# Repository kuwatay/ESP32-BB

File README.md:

# ESP32-BB

## 1. Introduction

**ESP32-BB** (Bearbone) is yet another ESP-32 based development board. 
For the programming of the board, an *extended 7-pin FTDI adapter* is required.

## 2. Schematic

## 3. Board layout

## 4. BOM

|     Name   |          Parts                    |   Value                 |
|  :-------: | :-------------------------------: | :---------------------: |
|     U1     |  3.3V Low voltage drop Regulator  | LM1117-3.3              | 
|     U2     |  ESP-WROOM-32                     | -                       | 
|  LED1,LED2 |  LED1 (Green)  LED2(RED)          | (1608 size)             | 
|     J1     |  2.1mm power Jack                 | Power in                | 
|     J2     |  7 pin                            | L-angle connector       | 
|   J3,J4    |  10Pin x 2 receptacle             | pin header is ok        | 
|  SW1,SW2   |  Tactile Switch                   | Alps SKHH or equivalent | 
|   Q1,Q2    |  NPN-TR                           | (2SC2712)               | 
|   R1,R3    |  Carbon Register                  | 10K Ohm 1/10W(1608)     | 
|   R7,R8    |  Carbon Register                  | 1K Ohm 1/10W(1608)      | 
| R9,R10,R11 |  Carbon Register                  | 10K Ohm 1/10W(1608)     | 
|   R12,R13  |  Carbon Register                  | 1K Ohm 1/10W(1608)      | 
|     C2     |  Multilayer Ceramic Capacitor     | 1nF / 10V  (1608)       |
|     C6     |  Electrolytic  Capacitor          | 100uF / 10V or better   |
|     C7     |  Electrolytic  Capacitor          | 10uF / 10V or better    |
|     C8     |  Multilayer Ceramic  Capacitor    | 0.1uF / 10V (1608)      |

## EOF

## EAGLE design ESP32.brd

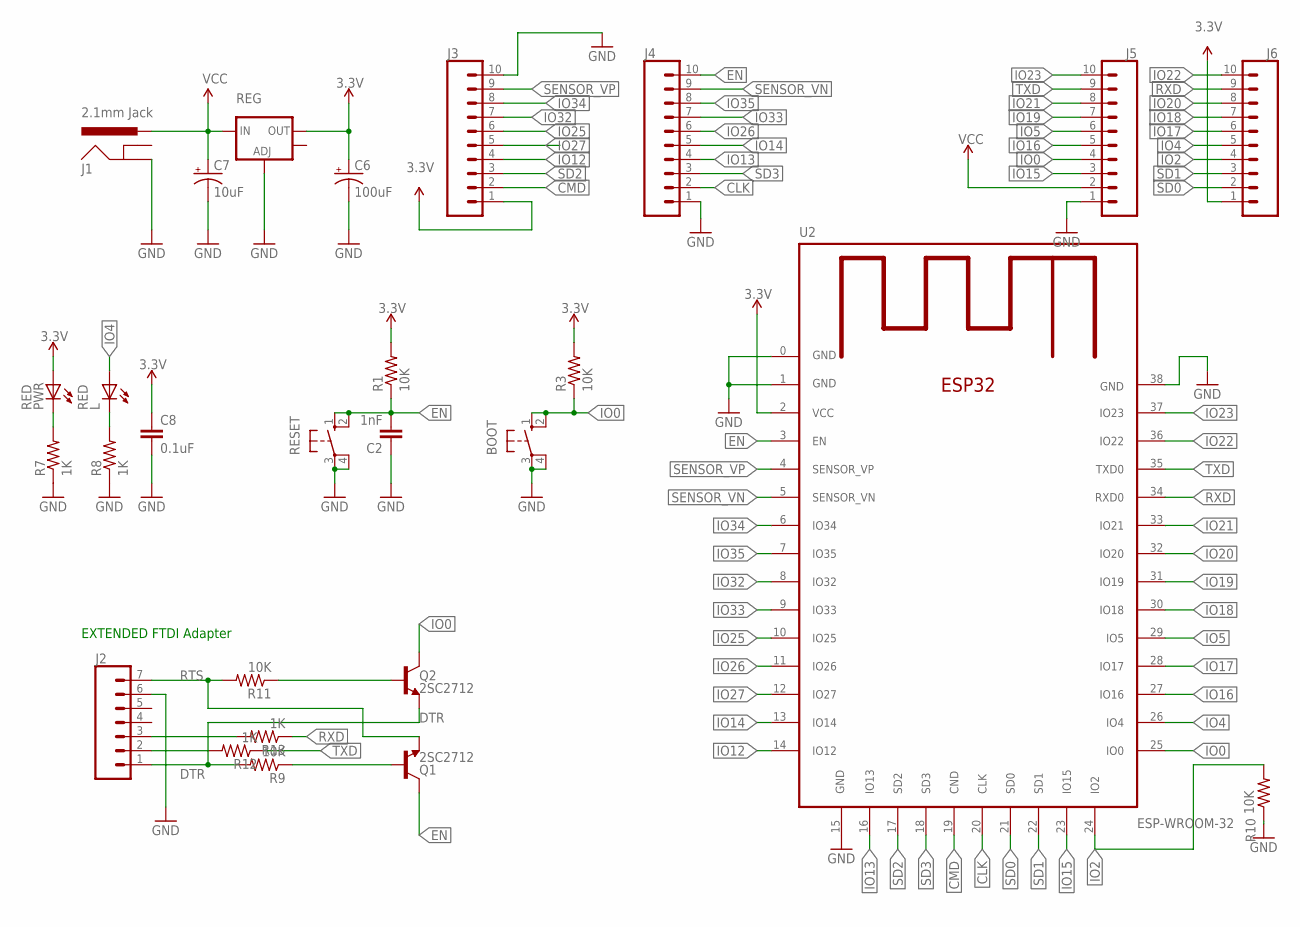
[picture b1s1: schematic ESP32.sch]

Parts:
BOOT: 10-XX; B3F-10XX
C2: 1nF; 0805
C6: 100uF; PANASONIC_D
C7: 10uF; PANASONIC_D
C8: 0.1uF; 0805
J1: 2.1mm Jack; POWER_JACK_PTH_LOCK
J2: CONN_07LOCK; 1X07_LOCK
J3, J4, J5, J6: CONN_10"; 1X10
L: RED; CHIP-LED0805
PWR: RED; CHIP-LED0805
Q1, Q2: 2SC2712; SOT23-3
R1, R3, R9, R10, R11: 10K; 0805
R7, R8, R12, R13: 1K; 0805
REG: V_REG_LM1117SOT223; SOT223
RESET: 10-XX; B3F-10XX
U2: ESP-WROOM-32; ESP32MOD

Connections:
3.3V: C6.+, C8.1, J3.1, J6.1, PWR.A, R1.2, R3.2, REG.2 (OUT), U2.2 (VCC)
B: Q2.1 (B), R11.1
CLK: J4.2, U2.20 (CLK)
CMD: J3.2, U2.19 (CND)
DTR: J2.1, Q2.2 (E), R9.2
EN: C2.2, J4.10, Q1.3 (C), R1.1, RESET.1 (S), RESET.2 (S1), U2.3 (EN)
GND: BOOT.3, BOOT.4 (P1), C2.1, C6.-, C7.-, C8.2, J1.GND, J2.6, J3.10, J4.1, J5.1, R7.1, R8.1, R10.1, REG.1 (ADJ), RESET.3, RESET.4 (P1), U2.0 (GND), U2.1 (GND), U2.15 (GND), U2.38 (GND)
IO0: BOOT.1 (S), BOOT.2 (S1), J5.4, Q2.3 (C), R3.1, U2.25 (IO0)
IO2: J6.4, R10.2, U2.24 (IO2)
IO4: J6.5, L.A, U2.26 (IO4)
IO5: J5.6, U2.29 (IO5)
IO12: J3.4, U2.14 (IO12)
IO13: J4.4, U2.16 (IO13)
IO14: J4.5, U2.13 (IO14)
IO15: J5.3, U2.23 (IO15)
IO16: J5.5, U2.27 (IO16)
IO17: J6.6, U2.28 (IO17)
IO18: J6.7, U2.30 (IO18)
IO19: J5.7, U2.31 (IO19)
IO20: J6.8, U2.32 (IO20)
IO21: J5.8, U2.33 (IO21)
IO22: J6.10, U2.36 (IO22)
IO23: J5.10, U2.37 (IO23)
IO25: J3.6, U2.10 (IO25)
IO26: J4.6, U2.11 (IO26)
IO27: J3.5, U2.12 (IO27)
IO32: J3.7, U2.8 (IO32)
IO33: J4.7, U2.9 (IO33)
IO34: J3.8, U2.6 (IO34)
IO35: J4.8, U2.7 (IO35)
unnamed: J2.2, R12.2
unnamed: J2.3, R13.2
unnamed: Q1.1 (B), R9.1
unnamed: PWR.C, R7.2
unnamed: L.C, R8.2
RTS: J2.7, Q1.2 (E), R11.2
RXD: J6.9, R13.1, U2.34 (RXD0)
SD0: J6.2, U2.21 (SD0)
SD1: J6.3, U2.22 (SD1)
SD2: J3.3, U2.17 (SD2)
SD3: J4.3, U2.18 (SD3)
SENSOR_VN: J4.9, U2.5 (SENSOR_VN)
SENSOR_VP: J3.9, U2.4 (SENSOR_VP)
TXD: J5.9, R12.1, U2.35 (TXD0)
VCC: C7.+, J1.PWR, J5.2, REG.3 (IN)

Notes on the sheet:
EXTENDED FTDI Adapter

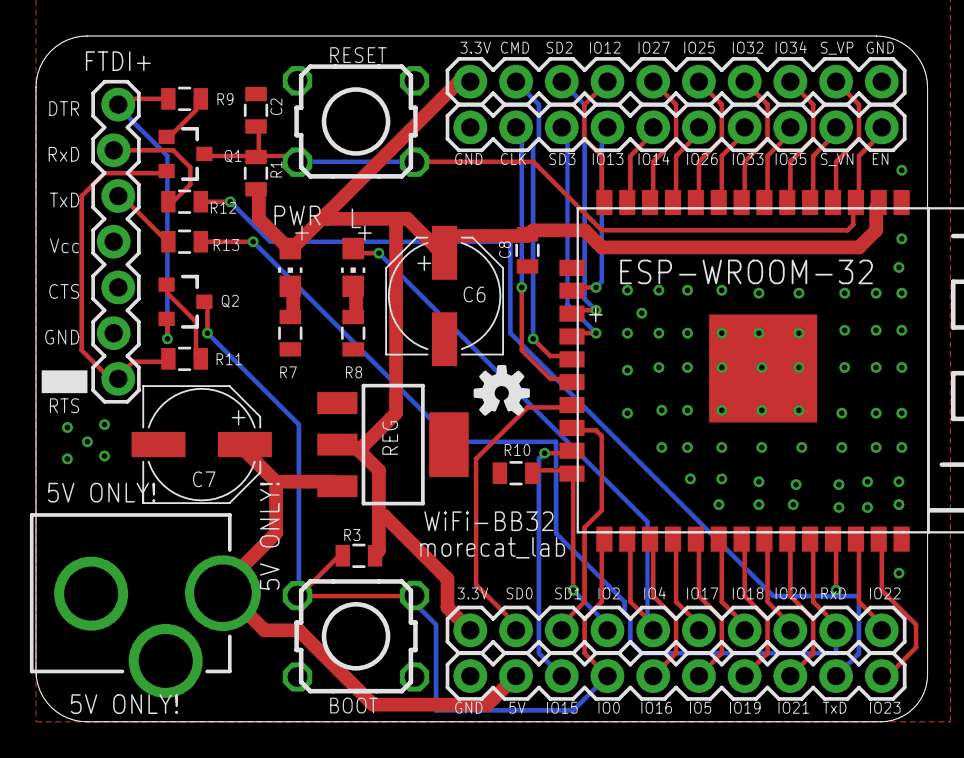
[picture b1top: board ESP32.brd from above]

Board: 4 copper layers, 49.5 x 38.1 mm, 29 parts (1 on the bottom side), 45 nets.

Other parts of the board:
U$2, U$3: OSHW-LOGO-S

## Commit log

2017-08-04 add photo
2017-08-08 add README
2017-08-08 modify link to image
2017-08-09 correct cap size

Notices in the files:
parts and their libraries:
SparkFun-Connectors: Licensing: CC v3.0 Share-Alike You are welcome to use this library for commercial purposes.
SparkFun-DiscreteSemi: Licensing: Creative Commons ShareAlike 4.0 International - https://creativecommons.org/licenses/by-sa/4.0
